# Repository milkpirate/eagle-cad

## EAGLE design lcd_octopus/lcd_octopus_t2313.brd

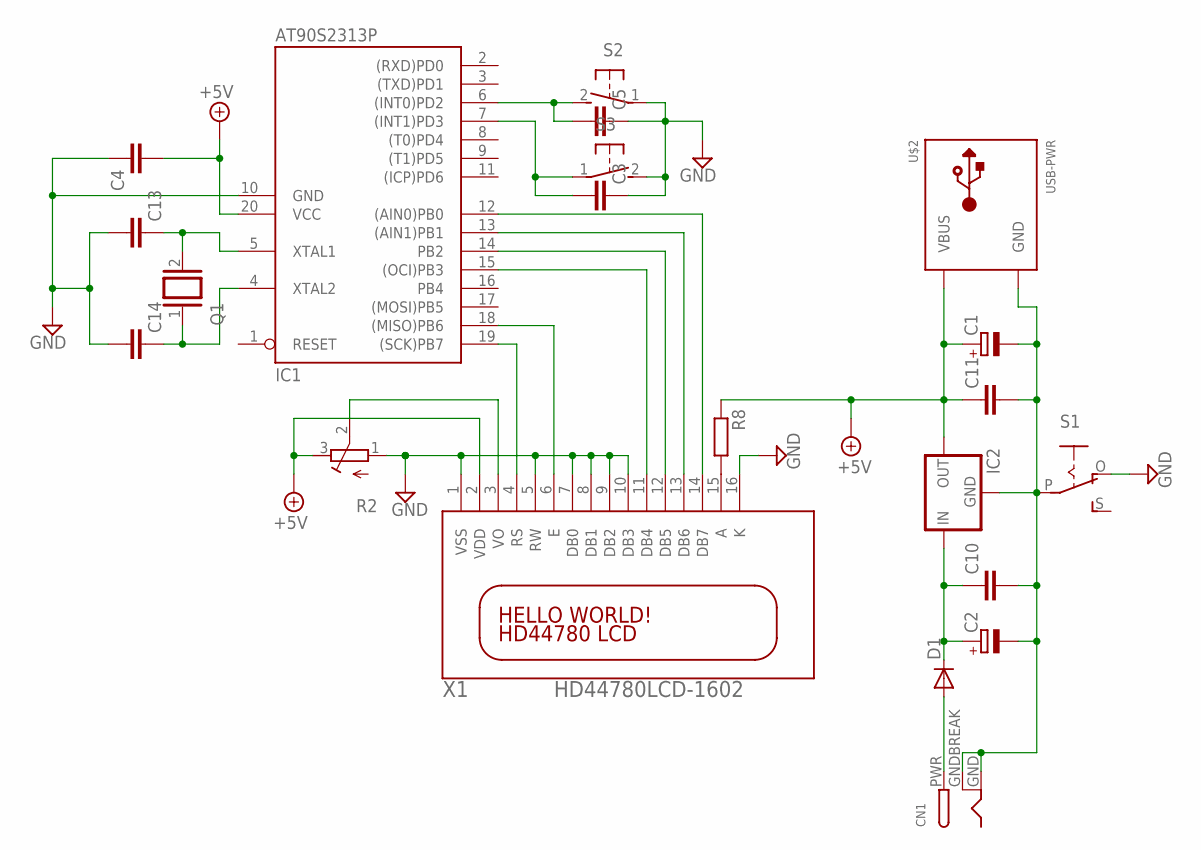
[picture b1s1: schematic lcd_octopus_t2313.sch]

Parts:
C1, C2: CPOL-EUTT2D5L; TT2D5L
C3, C4, C5, C10, C11, C13, C14: C-EU025-025X050; C025-025X050
CN1: DCBARRELPTH; DCJACK_2MM_PTH
D1: DIODE-D-2.5; D-2.5
IC1: AT90S2313P; DIL20
IC2: 78XX_V; 78XXV
Q1: XTAL/S; QS
R2: R-TRIMM3339P; RTRIM3339P
R8: R-EU_0207/10; 0207/10
S1: EG1218S; EG1218
S2, S3: 31-XX; B3F-31XX
U$2: USB-PWR; USB-MINIB-THM-MOLEX-PWRONLY
X1: HD44780LCD-1602; LCD1602

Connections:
+5V: C1.+, C4.2, C11.1, IC1.20 (VCC), IC2.OUT, R2.3 (E), R8.1, U$2.VBUS, X1.2 (VDD)
EN: IC1.18 ((MISO)PB6), X1.6 (E)
GND: C3.1, C4.1, C5.1, C13.2, C14.2, IC1.10 (GND), R2.1 (A), S1.O, S2.1, S3.2 (S), X1.1 (VSS), X1.5 (RW), X1.7 (DB0), X1.8 (DB1), X1.9 (DB2), X1.10 (DB3), X1.16 (K)
unnamed: C2.+, C10.1, D1.C, IC2.IN
unnamed: IC1.19 ((SCK)PB7), X1.4 (RS)
unnamed: IC1.15 ((OCI)PB3), X1.11 (DB4)
unnamed: IC1.14 (PB2), X1.12 (DB5)
unnamed: R8.2, X1.15 (A)
unnamed: IC1.13 ((AIN1)PB1), X1.13 (DB6)
unnamed: IC1.12 ((AIN0)PB0), X1.14 (DB7)
unnamed: R2.2 (S), X1.3 (VO)
unnamed: C1.-, C2.-, C10.2, C11.2, CN1.GND, CN1.GNDBREAK, IC2.GND, S1.P, U$2.GND
unnamed: C3.2, IC1.7 ((INT1)PD3), S3.1
unnamed: C13.1, IC1.5 (XTAL1), Q1.2
unnamed: C5.2, IC1.6 ((INT0)PD2), S2.2 (S)
unnamed: C14.1, IC1.4 (XTAL2), Q1.1
unnamed: CN1.PWR, D1.A

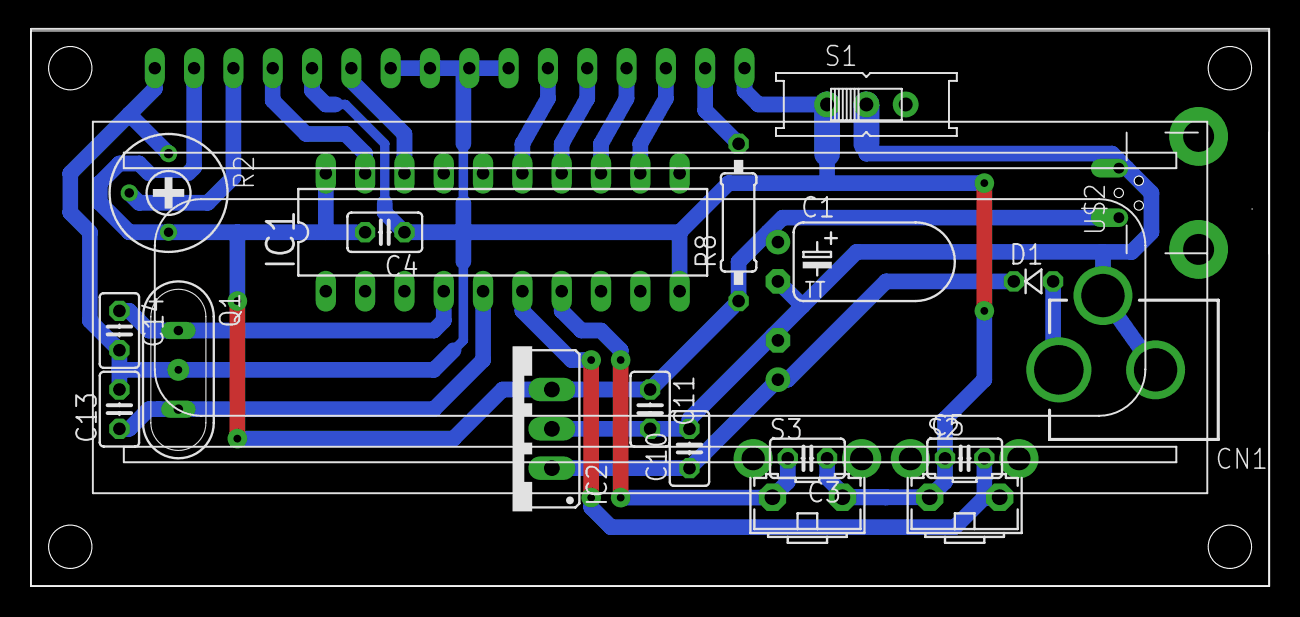
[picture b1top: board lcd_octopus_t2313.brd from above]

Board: 2 copper layers, 80.0 x 35.9 mm, 21 parts (1 on the bottom side), 17 nets.

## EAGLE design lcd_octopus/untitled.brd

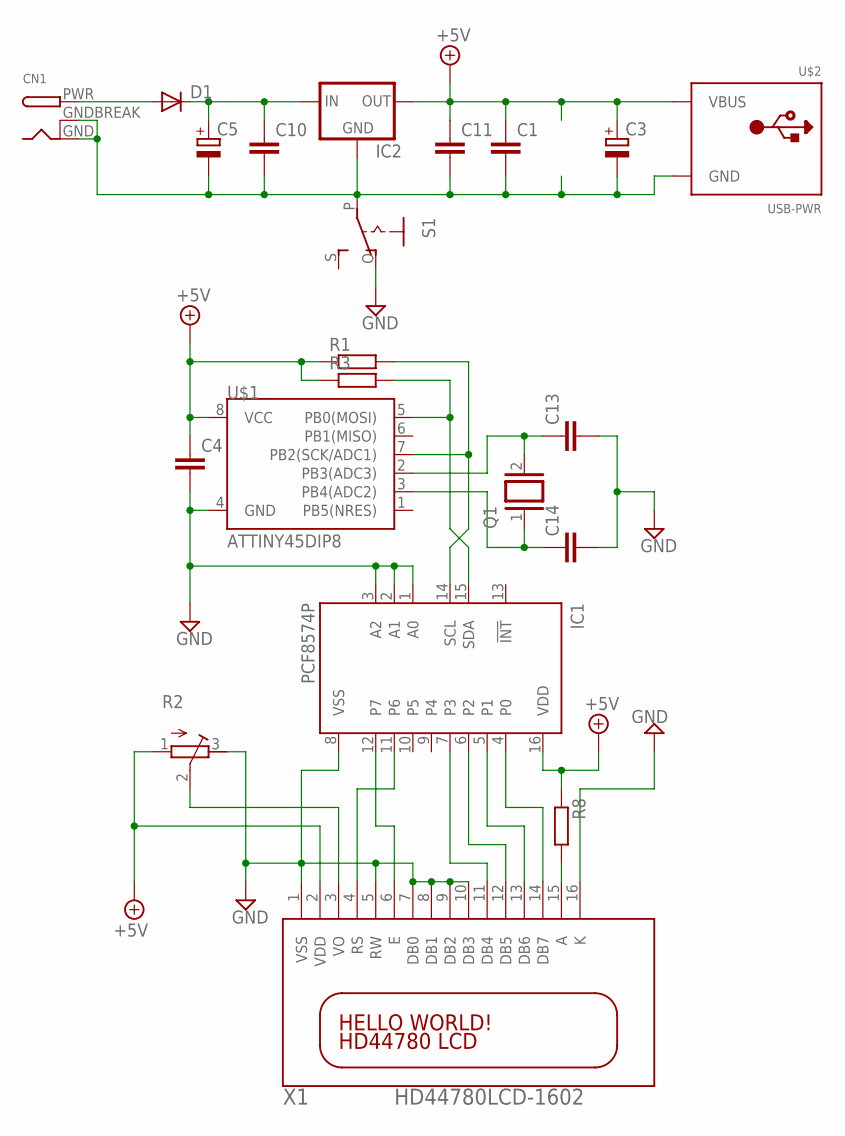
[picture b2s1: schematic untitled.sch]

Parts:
C1, C4, C10, C11, C13, C14: C-EU025-025X050; C025-025X050
C3, C5: CPOL-EUE2.5-6; E2,5-6
CN1: DCBARRELPTH; DCJACK_2MM_PTH
D1: DIODE-D-2.5; D-2.5
IC1: PCF8574P; DIL16
IC2: V_REG_78XXSIDE; 78XXL
Q1: XTAL/S; QS
R1: R-EU_0207/2V; 0207/2V
R2: R-TRIMM3339P; RTRIM3339P
R3: R-EU_0207/5V; 0207/5V
R8: R-EU_0207/10; 0207/10
S1: EG1218S; EG1218
U$1: ATTINY45DIP8; DIP08
U$2: USB-PWR; USB-MINIB-THM-MOLEX-PWRONLY
X1: HD44780LCD-1602; LCD1602

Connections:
+5V: C1.1, C3.+, C4.1, C11.1, IC1.16 (VDD), IC2.OUT, R1.1, R2.1 (A), R3.1, R8.1, U$1.8 (VCC), U$2.VBUS, X1.2 (VDD)
GND: C4.2, C13.2, C14.2, IC1.1 (A0), IC1.2 (A1), IC1.3 (A2), IC1.8 (VSS), R2.3 (E), S1.O, U$1.4 (GND), X1.1 (VSS), X1.5 (RW), X1.7 (DB0), X1.8 (DB1), X1.9 (DB2), X1.10 (DB3), X1.16 (K)
unnamed: C5.+, C10.1, D1.C, IC2.IN
unnamed: IC1.12 (P7), X1.6 (E)
unnamed: IC1.6 (P2), X1.12 (DB5)
unnamed: IC1.7 (P3), X1.11 (DB4)
unnamed: R8.2, X1.15 (A)
unnamed: IC1.5 (P1), X1.13 (DB6)
unnamed: IC1.4 (P0), X1.14 (DB7)
unnamed: R2.2 (S), X1.3 (VO)
unnamed: C1.2, C3.-, C5.-, C10.2, C11.2, CN1.GND, CN1.GNDBREAK, IC2.GND, S1.P, U$2.GND
unnamed: C13.1, Q1.2, U$1.2 (PB3(ADC3))
unnamed: IC1.11 (P6), X1.4 (RS)
unnamed: C14.1, Q1.1, U$1.3 (PB4(ADC2))
unnamed: CN1.PWR, D1.A
unnamed: IC1.15 (SDA), R3.2, U$1.5 (PB0(MOSI))
unnamed: IC1.14 (SCL), R1.2, U$1.7 (PB2(SCK/ADC1))

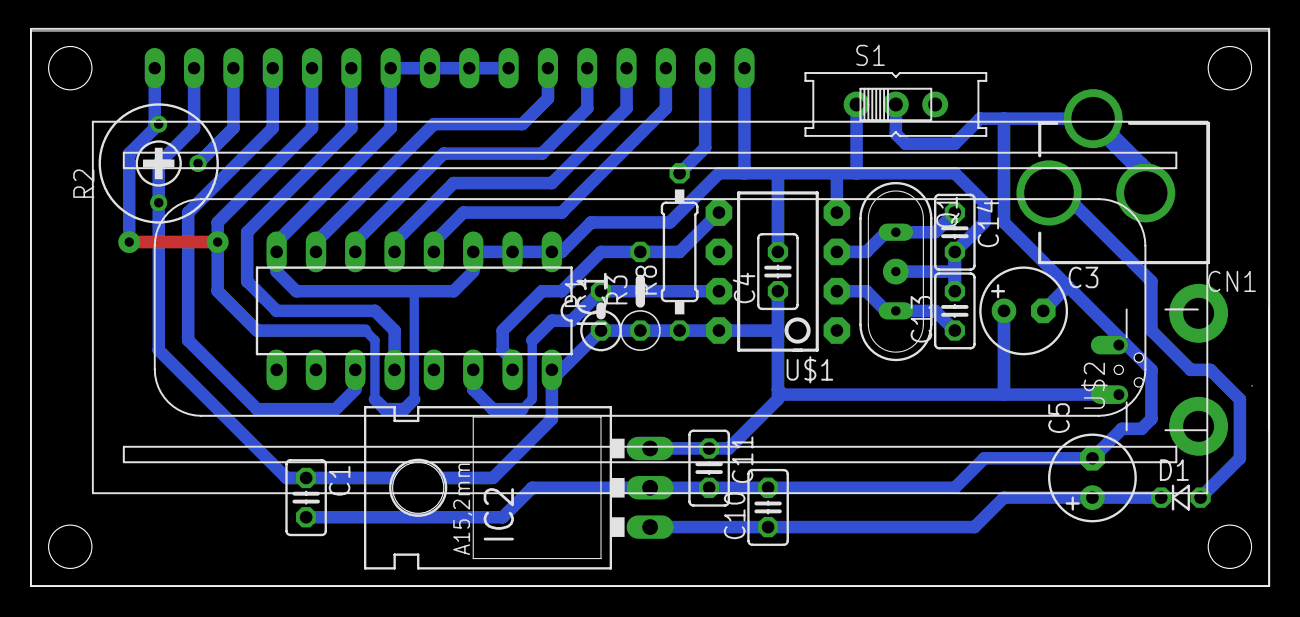
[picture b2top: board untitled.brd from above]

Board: 2 copper layers, 80.0 x 35.9 mm, 21 parts (0 on the bottom side), 17 nets.

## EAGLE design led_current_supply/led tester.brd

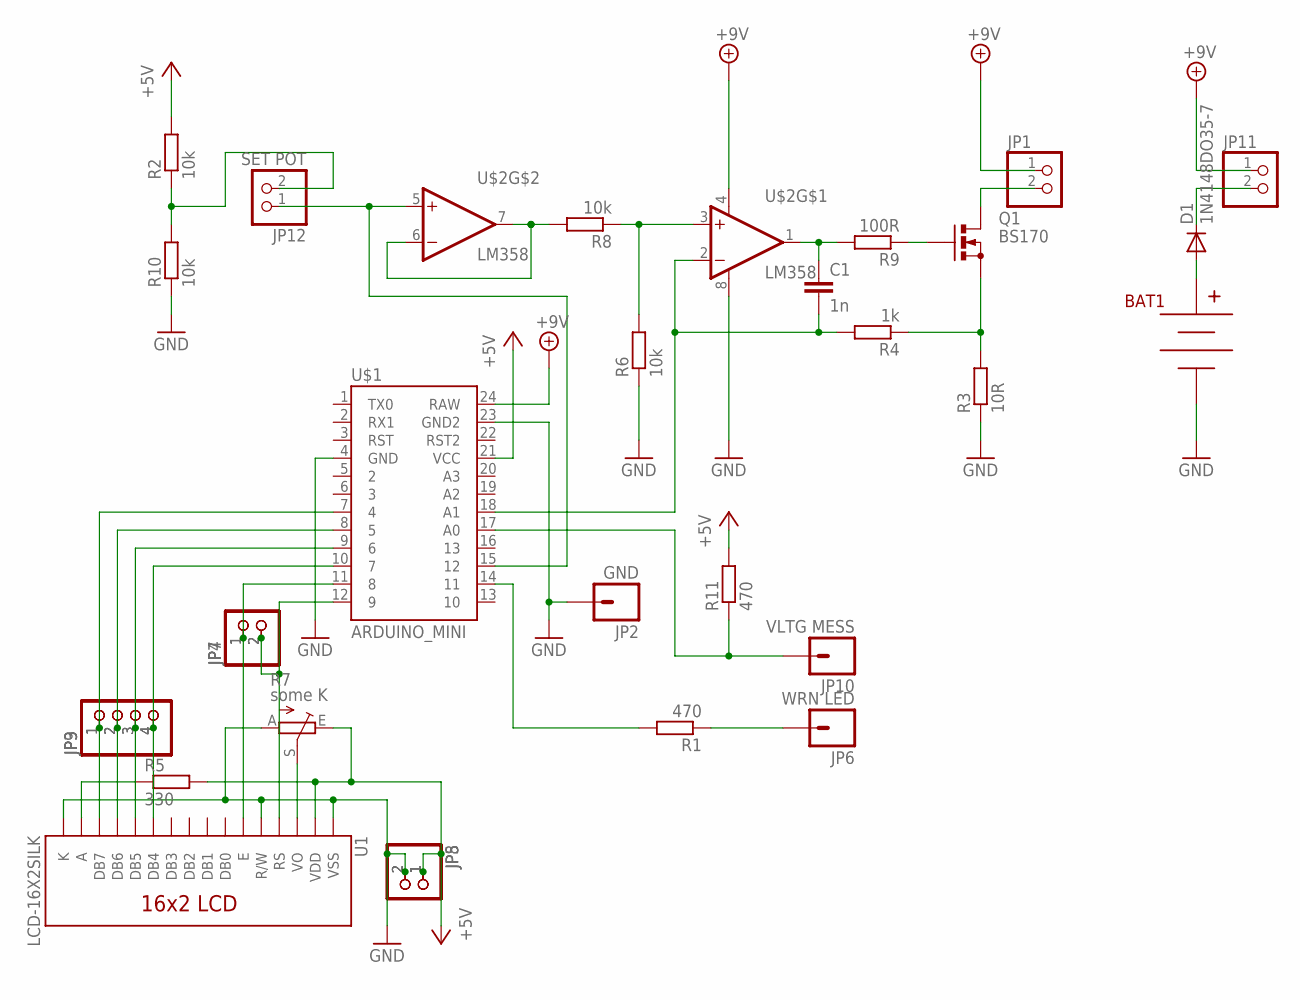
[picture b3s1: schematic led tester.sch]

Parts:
BAT1: BC9VPC
C1: 1n; C025-025X050
D1: 1N4148DO35-7; DO35-7
JP1, JP4, JP5, JP7, JP8, JP11: PINHD-1X2; 1X02
JP2: GND; 1X01_LONGPAD
JP3, JP9: PINHD-1X4; 1X04
JP6: WRN LED; 1X01_LONGPAD
JP10: VLTG MESS; 1X01_LONGPAD
JP12: SET POT; 1X02
Q1: BS170; SOT54E
R1, R11: 470; 0204/7
R2, R6, R8, R10: 10k; 0204/7
R3: 10R; 0207/10
R4: 1k; 0204/7
R5: 330; 0204/7
R7: some K; S63P
R9: 100R; 0204/7
U1: LCD-16X2SILK; LCD-16X2
U$1: ARDUINO_MINI
U$2: LM358; DIP08

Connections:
+5V: JP5.1, JP8.1, R2.2, R5.2, R7.E, R11.2, U1.2 (VDD), U$1.21 (VCC)
+9V: JP1.1, JP11.1, U$1.24 (RAW), U$2.4 (V-)
GND: BAT1.V-, JP2.1, JP5.2, JP8.2, R3.1, R6.1, R7.A, R10.1, U1.1 (VSS), U1.5 (R/W), U1.16 (K), U$1.4 (GND), U$1.23 (GND2), U$2.8 (V+)
unnamed: Q1.S, R3.2, R4.1
unnamed: JP1.2, Q1.D
unnamed: JP10.1, R11.1, U$1.17 (A0)
unnamed: R6.2, R8.1, U$2.3 (+IN)
unnamed: R8.2, U$2.6 (-IN), U$2.7 (OUT)
unnamed: JP12.2, R2.1, R10.2
unnamed: D1.C, JP11.2
unnamed: R1.2, U$1.14 (11)
unnamed: BAT1.V+, D1.A
unnamed: JP6.1, R1.1
unnamed: JP12.1, U$1.15 (12), U$2.5 (+IN)
unnamed: R7.S, U1.3 (VO)
unnamed: R5.1, U1.15 (A)
unnamed: C1.1, R9.2, U$2.1 (OUT)
unnamed: C1.2, R4.2, U$1.18 (A1), U$2.2 (-IN)
unnamed: JP4.2, JP7.2, U1.4 (RS), U$1.12 (9)
unnamed: JP4.1, JP7.1, U1.6 (E), U$1.11 (8)
unnamed: JP3.4, JP9.4, U1.11 (DB4), U$1.10 (7)
unnamed: JP3.3, JP9.3, U1.12 (DB5), U$1.9 (6)
unnamed: JP3.2, JP9.2, U1.13 (DB6), U$1.8 (5)
unnamed: JP3.1, JP9.1, U1.14 (DB7), U$1.7 (4)
unnamed: Q1.G, R9.1

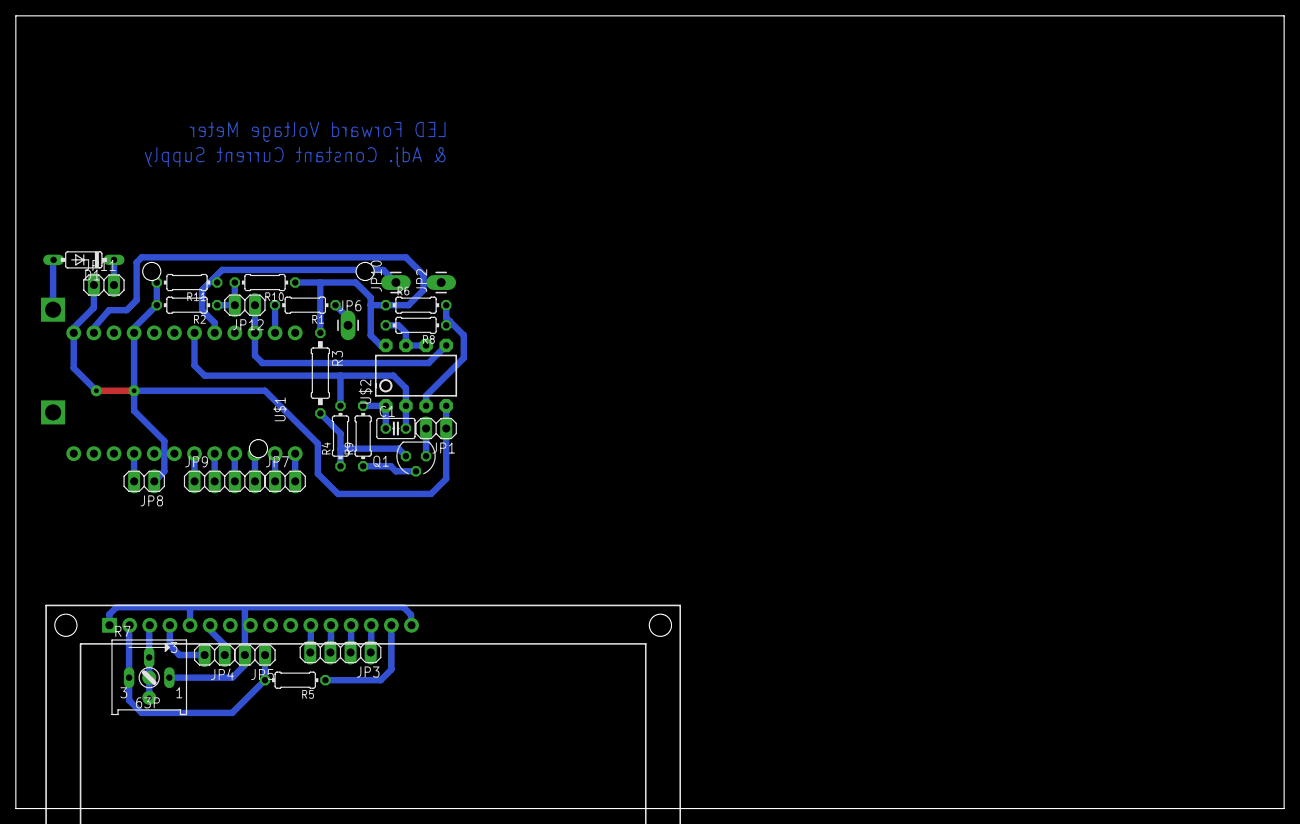
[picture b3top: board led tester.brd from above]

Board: 2 copper layers, 160.0 x 100.0 mm, 30 parts (1 on the bottom side), 25 nets.

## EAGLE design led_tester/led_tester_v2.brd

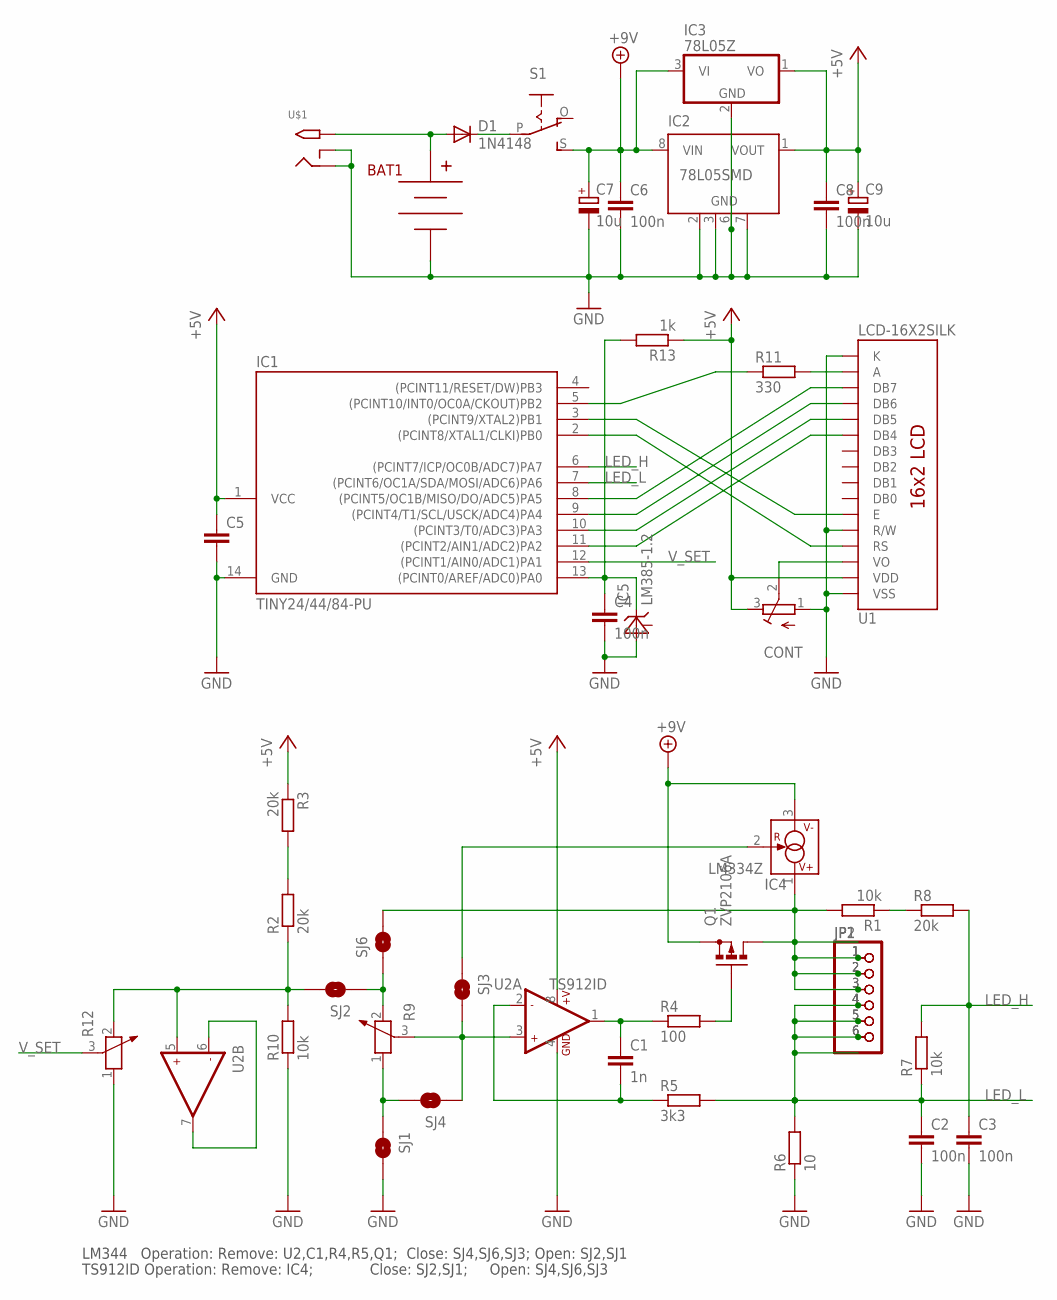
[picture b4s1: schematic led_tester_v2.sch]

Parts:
BAT1: BC9VPCKIT_SOLDERMASK; BC9VPC_KIT
C1: 1n; C025-025X050
C2, C3, C4, C6, C8: 100n; C025-025X050
C5: C-EU025-025X050; C025-025X050
C7, C9: 10u; E2,5-6E
CONT: R-TRIMM3296P; RTRIM3296P
D1: 1N4148; D-10
IC1: TINY24/44/84-PU; DIL14
IC2: 78L05SMD; SO08
IC3: 78L05Z; TO92
IC4: LM334Z; TO92
IC5: LM385-1.2; TO92-
JP1, JP2: PINHD-1X6; 1X06
Q1: ZVP2106A; TO92-OVAL
R1, R7, R10: 10k; 0204/7
R2, R3, R8: 20k; 0204/7
R4: 100; 0204/7
R5: 3k3; 0204/7
R6: 10; 0204/7
R9, R12: POTENTIOMETER_PT-10S; PT-10S
R11: 330; 0204/7
R13: 1k; 0204/7
S1: EG1218S; EG1218
SJ1, SJ2, SJ3, SJ4, SJ6: SOLDERJUMPERNO; SJ_2S-NO
U1: LCD-16X2SILK; LCD-16X2
U2: TS912ID; SO08
U$1: 2.1MMJACKTHM; PJ-102A

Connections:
+5V: C5.1, C8.1, C9.+, CONT.3 (E), IC1.1 (VCC), IC2.1 (VOUT), IC3.1 (VO), R3.1, R13.1, U1.2 (VDD), U2.8 (+V)
+9V: C6.1, C7.+, IC2.8 (VIN), IC3.3 (VI), IC4.3 (V-), Q1.1 (S), S1.S
ANODE: IC4.1 (V+), JP1.1, JP1.2, JP1.3, JP2.1, JP2.2, JP2.3, Q1.3 (D), R1.2, SJ6.2
GND: BAT1.V+ (V-), C2.2, C3.2, C4.2, C5.2, C6.2, C7.-, C8.2, C9.-, CONT.1 (A), IC1.14 (GND), IC2.2 (GND), IC2.3 (GND), IC2.6 (GND), IC2.7 (GND), IC3.2 (GND), IC5.1 (A), R6.1, R10.1, R12.1, SJ1.2, U1.1 (VSS), U1.5 (R/W), U1.16 (K), U2.4 (GND), U$1.RING, U$1.RING_SW
LED_H: C3.1, IC1.6 ((PCINT7/ICP/OC0B/ADC7)PA7), R7.2, R8.2
LED_L: C2.1, IC1.7 ((PCINT6/OC1A/SDA/MOSI/ADC6)PA6), JP1.4, JP1.5, JP1.6, JP2.4, JP2.5, JP2.6, R5.2, R6.2, R7.1
unnamed: IC1.8 ((PCINT5/OC1B/MISO/DO/ADC5)PA5), U1.14 (DB7)
unnamed: IC1.9 ((PCINT4/T1/SCL/USCK/ADC4)PA4), U1.13 (DB6)
unnamed: IC1.10 ((PCINT3/T0/ADC3)PA3), U1.12 (DB5)
unnamed: IC1.11 ((PCINT2/AIN1/ADC2)PA2), U1.11 (DB4)
unnamed: IC1.2 ((PCINT8/XTAL1/CLKI)PB0), U1.4 (RS)
unnamed: IC1.3 ((PCINT9/XTAL2)PB1), U1.6 (E)
unnamed: C1.1, R4.1, U2.1 (OUT1)
unnamed: Q1.2 (G), R4.2
unnamed: D1.C, S1.P
unnamed: R9.2, SJ2.1, SJ6.1
unnamed: R2.1, R10.2, R12.2, SJ2.2, U2.5 (+IN2)
unnamed: C1.2, R5.1, U2.2 (-IN1)
unnamed: U2.6 (-IN2), U2.7 (OUT2)
unnamed: R1.1, R8.1
unnamed: CONT.2 (S), U1.3 (VO)
unnamed: BAT1.V- (V+), D1.A, U$1.TIP
unnamed: R11.2, U1.15 (A)
unnamed: IC4.2 (R), SJ3.1
unnamed: R2.2, R3.2
unnamed: IC1.5 ((PCINT10/INT0/OC0A/CKOUT)PB2), R11.1
unnamed: R9.1, SJ1.1, SJ4.2
unnamed: R9.3, SJ3.2, SJ4.1, U2.3 (+IN1)
unnamed: C4.1, IC1.13 ((PCINT0/AREF/ADC0)PA0), IC5.2 (C), R13.2
V_SET: IC1.12 ((PCINT1/AIN0/ADC1)PA1), R12.3

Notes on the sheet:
LM344 Operation: Remove: U2,C1,R4,R5,Q1; Close: SJ4,SJ6,SJ3; Open: SJ2,SJ1
TS912ID Operation: Remove: IC4; Close: SJ2,SJ1; Open: SJ4,SJ6,SJ3

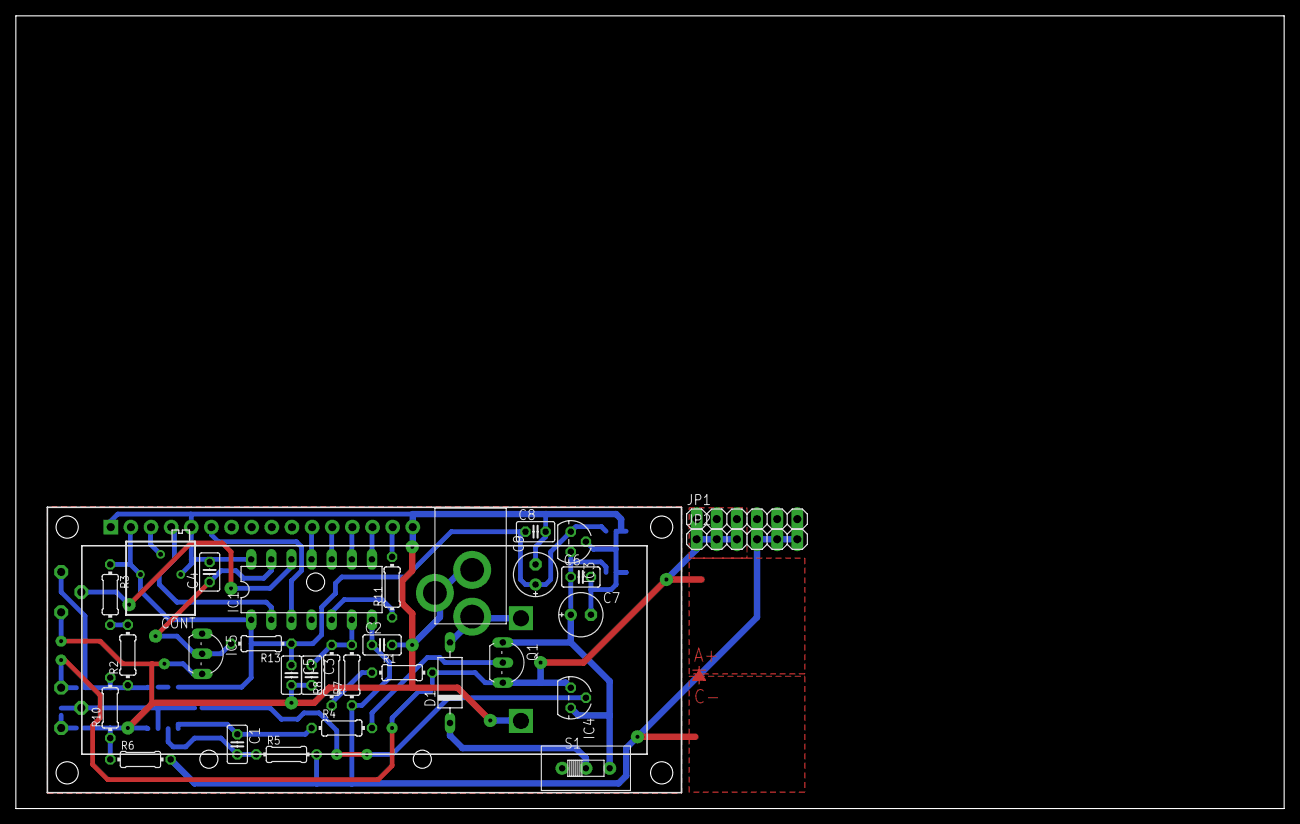
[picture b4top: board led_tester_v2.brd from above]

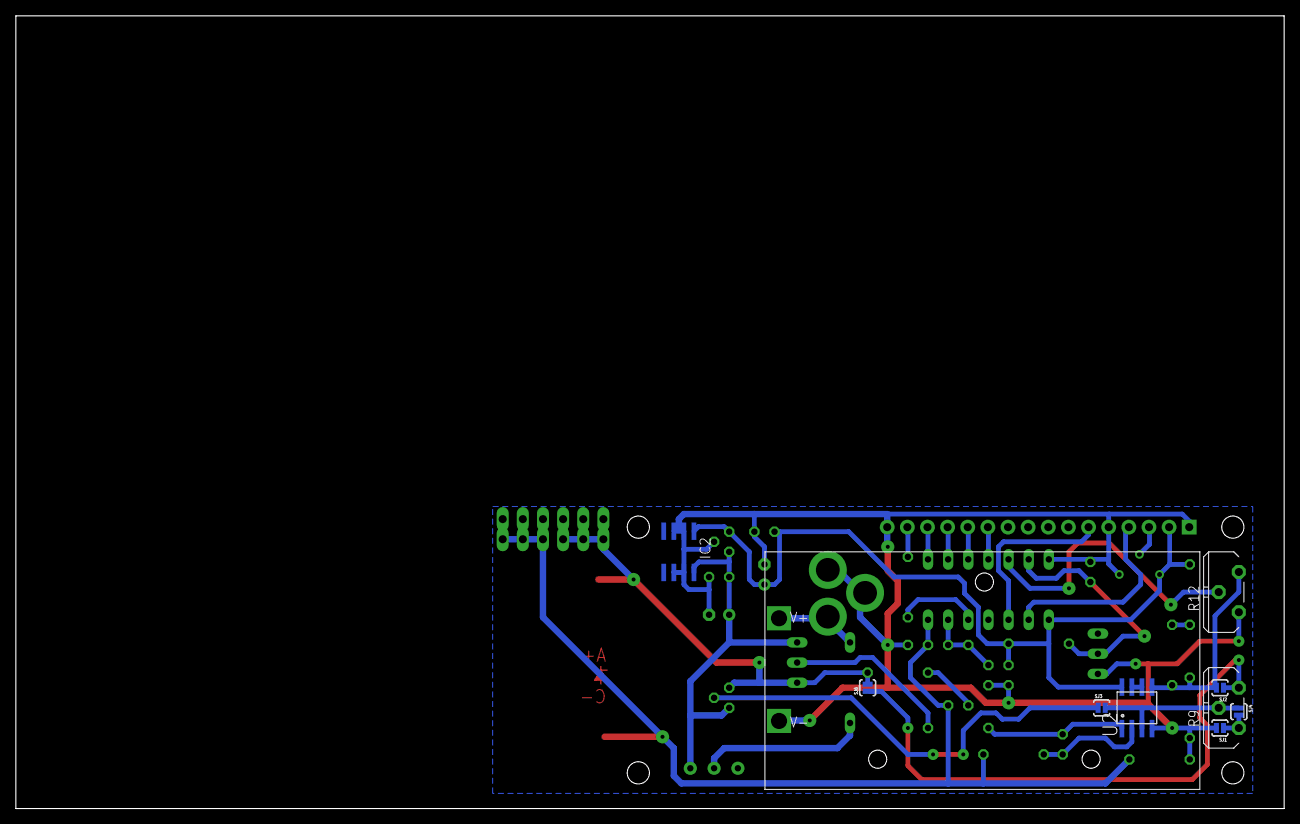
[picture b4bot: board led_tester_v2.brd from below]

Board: 2 copper layers, 160.0 x 100.0 mm, 42 parts (10 on the bottom side), 30 nets.

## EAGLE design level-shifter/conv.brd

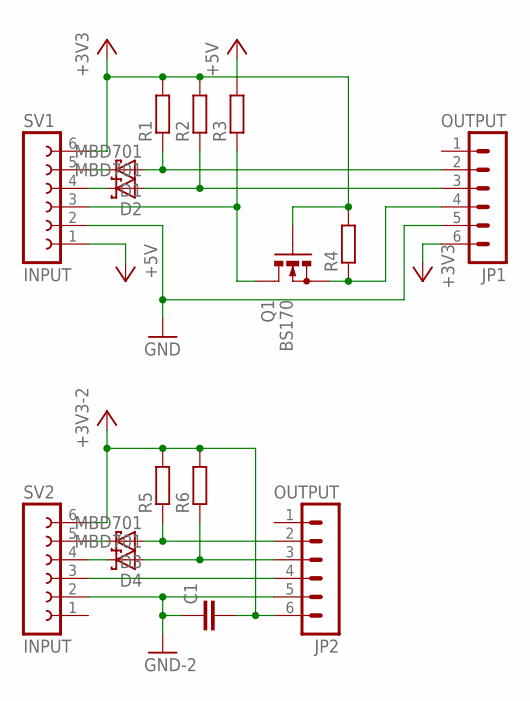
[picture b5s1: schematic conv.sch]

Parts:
C1: C-EU025-025X050; C025-025X050
D1, D2, D3, D4: MBD701; TO92H
JP1, JP2: OUTPUT; MA06-1
Q1: BS170; SOT54E
R1, R4, R5: R-EU_0207/2V; 0207/2V
R2, R3, R6: R-EU_0207/5V; 0207/5V
SV1, SV2: INPUT; FE06W

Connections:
+3V3: C1.2, JP1.6, JP2.6, Q1.G, R1.2, R2.2, R4.2, R5.2, R6.2, SV1.6, SV2.6
+5V: SV1.1
+5V-1: R3.2
GND: C1.1, JP1.5, JP2.5, SV1.2, SV2.2
H-RST: D1.2 (C), SV1.5
H-RST1: D3.2 (C), SV2.5
H-RX: Q1.D, R3.1, SV1.3
H-TX: D2.2 (C), SV1.4
H-TX1: D4.2 (C), SV2.4
L-RST: D1.1 (A), JP1.2, R1.1
L-RST1: D3.1 (A), JP2.2, R5.1
L-RX: JP1.4, Q1.S, R4.1
L-RX1: JP2.4, SV2.3
L-TX: D2.1 (A), JP1.3, R2.1
L-TX1: D4.1 (A), JP2.3, R6.1

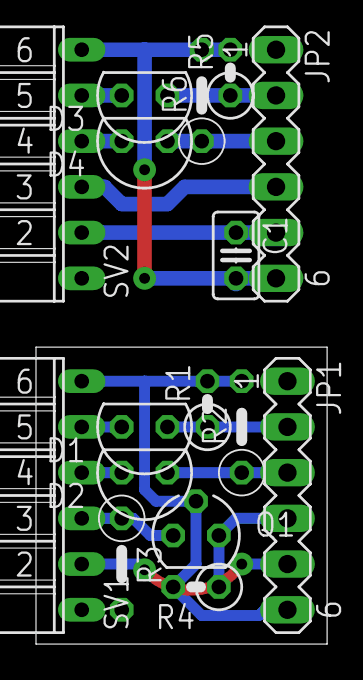
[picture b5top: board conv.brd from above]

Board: 2 copper layers, 16.2 x 16.5 mm, 16 parts (0 on the bottom side), 13 nets.

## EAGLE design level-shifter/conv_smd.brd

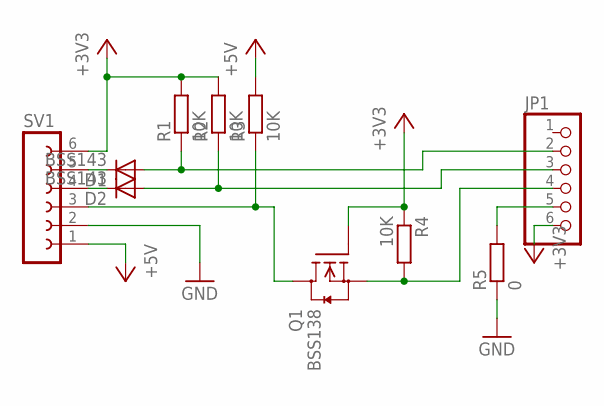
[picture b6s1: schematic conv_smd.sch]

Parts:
D1, D2: BSS143; SOD80C
JP1: PINHD-1X6/90; 1X06/90
Q1: BSS138; SOT23
R1, R2, R4: 10K; M0805
R3: 10K; M1206
R5: 0; M1206
SV1: FE06W

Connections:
+3V3: JP1.6, Q1.1 (G), R1.2, R2.2, R4.1, SV1.6
+5V: R3.2, SV1.1
GND: R5.1, SV1.2
H-RST: D1.C, SV1.5
H-RX: Q1.3 (D), R3.1, SV1.3
H-TX: D2.C, SV1.4
L-RST: D1.A, JP1.2, R1.1
L-RX: JP1.4, Q1.2 (S), R4.2
L-TX: D2.A, JP1.3, R2.1
unnamed: JP1.5, R5.2

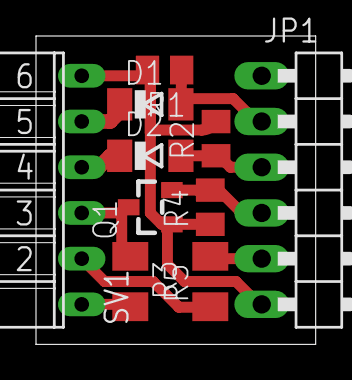
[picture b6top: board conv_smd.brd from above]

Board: 2 copper layers, 15.5 x 17.1 mm, 10 parts (0 on the bottom side), 10 nets.

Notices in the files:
parts and their libraries:
SparkFun: Licensing: CC v3.0 Share-Alike You are welcome to use this library for commercial purposes.
SparkFun-Displays: Licensing: Creative Commons ShareAlike 4.0 International - https://creativecommons.org/licenses/by-sa/4.0
m-pad-2.1: License : GNU General Public License version 2 (see bottom)
